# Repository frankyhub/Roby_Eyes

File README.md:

<div align="center">

|[:skull:ISSUE](https://github.com/frankyhub/Roby_Eyes/issues?q=is%3Aissue)|[:speech_balloon: Forum /Discussion](https://github.com/frankyhub/Roby_Eyes/discussions)|[:grey_question:WiKi](https://github.com/frankyhub/Roby_Eyes/wiki)||
|--|--|--|--|
| | | | |
<a href="https://github.com/frankyhub/Roby_Eyes/issues">|<a href="https://github.com/frankyhub/Roby_Eyes/discussions">|<a href="https://github.com/frankyhub/Roby_Eyes/6eleases">||
|| <a href="https://github.com/frankyhub/Roby_Eyes/pulse" alt="Activity">| <a href="https://github.com/frankyhub/Roby_Eyes/graphs/traffic">  |<a href="https://github.com/frankyhub?tab=stars"> ||

# Roby_Eyes

<br> <br>

## Story:
Das Repo beschreibt den Roby_Eyes, er hat zwei MAX7219 Displays für die Augen und er kann laufen, tanzen und den Moonwalk. Jedes Bein hat zwei Gelenke, die von Servo-Motoren bewegt werden. Als Steuerung dient ein Arduino NANO, gespeist von einer 9V-Batterie.
Die Roby_Eyes-Elemente werden aus einer 3mm Sperrholzplatte gelasert.

## Die Stückliste:

| Anzahl | Bezeichnung | 
| -------- | -------- | 
| 1  | Sperrholzplatte 300x600x3mm  | 
|  1 | NANO-Shield  | 
| 1  | Arduino NANO V3  | 
| 1  |  40 Pin Male 2,54mm Stiftleisten einreihig für das NANO-Shield | 
|  1 |  40 Pin Female 2,54 mm Buchsenleiste einreihig für das NANO-Shield | 
| 1  | Schalter 1 polig  | 
| 2  | MAX7219 Displays  | 
| 1  | 9V Batterie  | 
| 1  | 9V Batterie-Klipp  | 
| 4  | Servo Motore SG90  | 
| 2  | Zylinderkopf Schrauben M3x8  | 
| 1  | Kabelbinder 10cm  | 
| 1  | Holzleim  | 
| 1  | Sekundenkleber  | 
| 1  | 20cm Schaltlitze 0,25mm2  | 

## Der NANO mit Shield und Stiftleisten

<br> <br>

## Aufbau und Montage

Der Aufbau und die Montage von Robi ist in mehrere Schritte unterteilt

## Schritt 1: 

Verwende die Lasercutter Vorlage, bestehend aus, Kopfteil, Füße und Schuhe

<br> <br>

## Schritt 2: 

Das Kopfteil montieren. Die Deckplatte noch nicht verkleben.

<br> <br>

## Schritt 3: 

Die Hülle der beiden Füße verkleben.
Achtung: Wir benötigen zwei Füße. Die Öffnungen für die Servokabel sind jeweils innen und die Servos zeigen nach vorne!

<br> <br>

<br> <br>

<br> <br>

Die beiden Oberteile der Füße deckungsgleich verkleben (noch nicht an die Füße kleben!).

<br> <br>

Die Oberteile der Füße werden an den Servo im Kopfteil geschraubt.

Alternativ können zu besseren Stabilität auch die 3D-Druck Teile verwendet werden.

<br> <br>

## Schritt 4: 
Den Robi verdrahten, die Bauteile jedoch noch nicht in das Gehäuse montieren.

<br> <br>

|	Servo	|	NANO|
| -------- | -------- | 
| Servo rechts oben| D5|
| Servo rechts unten | D6 |
| Servo links oben | D8 |
| Servo links unten  |D9 |
| -------- | -------- | 

<br> <br>

<br> <br>

<br> <br>

  |  MAX72xx | NANO |
| -------- | -------- | 
|    VCC | 5V|
|    GND| GND|
 |   DIN | D11|
|    CS |  D10|
|    CLK | D13|
| -------- | -------- | 

## Schritt 5: 
Wir starten den ersten Funktionstest. Den NANO mit der Arduino IDE (Robi_tanzt.ino) programmieren. Es stehen auch Testprogramme für die Servos und das LED-Display zur Verfügung.

Im Robi_tanzt.ino Programm kann zur korrekten Position der Servos der CALIBRATION-Modus gewählt werden (Programmzeile 233).

Ist der Robi programmiert und sind die Servos in 90° Stellung, können sie in das Kopfteil und in die Füße montiert werden.

## Schritt 6: 
Die beiden Servos in 90° Stellung mit den unteren Kopfteil und den Oberteil der Füße verschrauben. Die Servos sollten durch die Verschraubung fest am Kopfteil sitzen. Anschließend die 9V-Batterie mit den Kabelbinder befestigen.

<br> <br>

Die Schrittmotore in die Fußhülle montieren und das Fuß Unterteil ankleben

<br> <br>

Die Schuhe an die Füße montieren

<br> <br>

Die Servo-Kabel in den Body führen und die Füße an die Fußoberteile kleben

<br> <br>

Alternativ können zu besseren Stabilität auch die 3D-Druck Teile verwendet werden.

<br> <br>

## Schritt 7: 

Das "RUN" Programm in den NANO laden.

Es stehen 3 Programm-Modis zur Verfügung.

In der Programmzeile 233 den "RUN" Modus auswählen:

+ //#define INSTALL
+ //#define CALIBRATION
+ #define RUN

Ist der erste Funktionstest erfolgreich, kleben wir die 3D Druck Abstandshalter auf das NANO-Shield und kleben den NANO 
mit Shield, das LED-Display in das Kopfteil und montieren den Schalter in die Kopfteil Platte. Das Kopfteil jetzt 
vollständig zusammenbauen.

</div>

<div align="center">
  
## Schritt 8

Es stehen auch 3D-Druck Arme zur Verfügung, die an das Kopfteil geklebt werden. 

Jetzt kann Roby tanzen.

<br> <br>
  
---

## Servo-Motor Impulsdiagramme:

<br> <br>

Impulsdiagramm: Ansteuerung des Servos mit einer Frequenz von 50 Hz:

<br> <br>

Impulsdiagramm: Ansteuerung des Servos mit einer Impulsbreite von 2,5ms (180°):

<br> <br>

---

<div style="position:absolute; left:2cm; ">   
<ol class="breadcrumb" style="border-top: 2px solid black;border-bottom:2px solid black; height: 45px; width: 900px;"> <p align="center"><a href="#oben">nach oben</a></p></ol>
</div>  

---

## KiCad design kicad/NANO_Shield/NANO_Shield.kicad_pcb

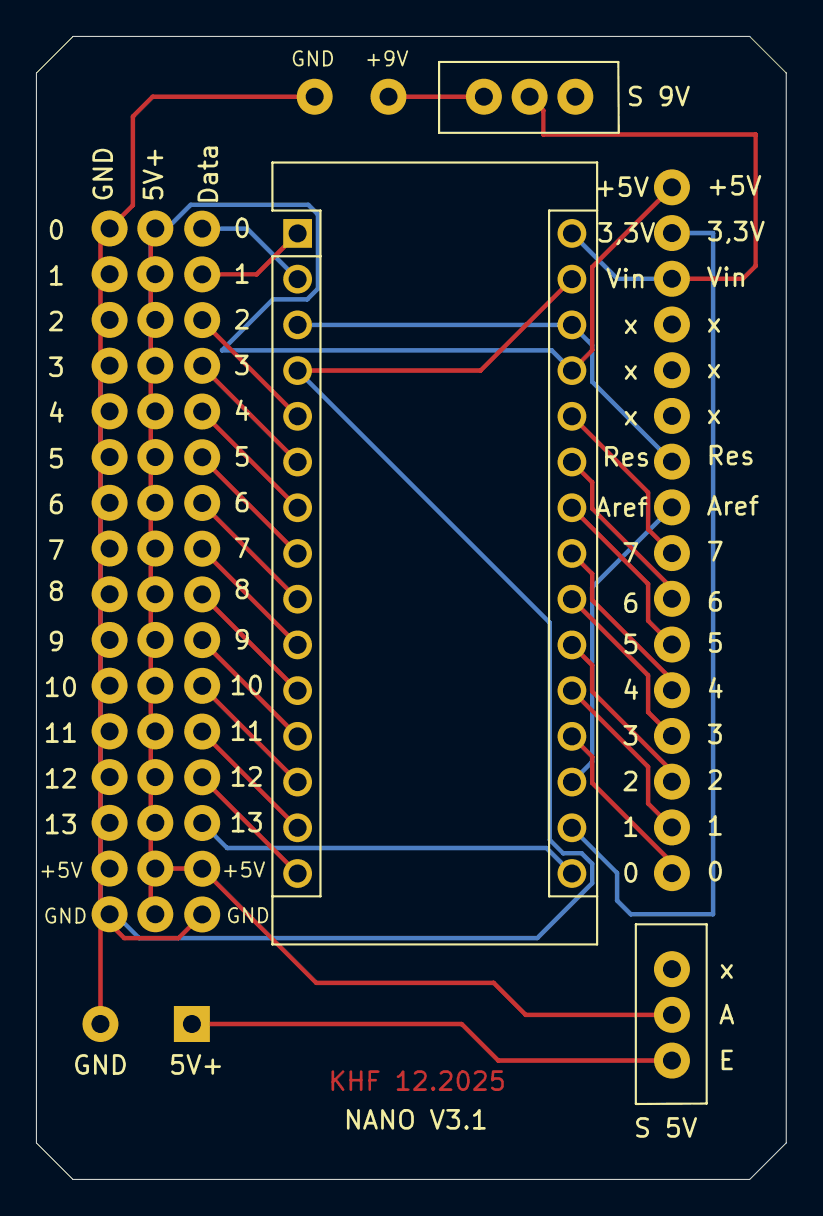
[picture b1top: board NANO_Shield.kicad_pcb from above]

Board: 2 copper layers, 41.7 x 63.5 mm, 8 parts (0 on the bottom side), 29 nets.

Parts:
A1: Arduino_Nano_v3.x; Arduino_Nano
GND: 9VBat; 9VBAT_khf
J1, J2, J3, J4: NANO16PINStiftleiste; NANO_Stift_16PIN
S 5V, S 9V: Micro_Schalter; Micro_SchalterKHF

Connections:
unnamed: A1.1, J3.2
unnamed: A1.2, J3.1
unnamed: A1.5, J3.3
unnamed: A1.6, J3.4
unnamed: A1.7, J3.5
unnamed: A1.8, J3.6
unnamed: A1.9, J3.7
unnamed: A1.10, J3.8
unnamed: A1.11, J3.9
unnamed: A1.12, J3.10
unnamed: A1.13, J3.11
unnamed: A1.14, J3.12
unnamed: A1.15, J3.13
unnamed: A1.16, J3.14
unnamed: A1.17, J4.15
unnamed: A1.18, J4.9
unnamed: A1.19, J4.1
unnamed: A1.20, J4.2
unnamed: A1.21, J4.3
unnamed: A1.22, J4.4
unnamed: A1.23, J4.5
unnamed: A1.24, J4.6
unnamed: A1.25, J4.7
unnamed: A1.26, J4.8
unnamed: A1.27, J2.1, J2.2, J2.3, J2.4, J2.5, J2.6, J2.7, J2.8, J2.9, J2.10, J2.11, J2.12, J2.13, J2.14, J2.15, J2.16, J3.15, J4.16, S 5V.2
unnamed: A1.3, A1.28, J4.10
unnamed: A1.4, A1.29, GND.1, J1.1, J1.2, J1.3, J1.4, J1.5, J1.6, J1.7, J1.8, J1.9, J1.10, J1.11, J1.12, J1.13, J1.14, J1.15, J1.16, J3.16
unnamed: A1.30, J4.14, S 9V.2, S 9V.3
unnamed: GND.2, S 5V.1
